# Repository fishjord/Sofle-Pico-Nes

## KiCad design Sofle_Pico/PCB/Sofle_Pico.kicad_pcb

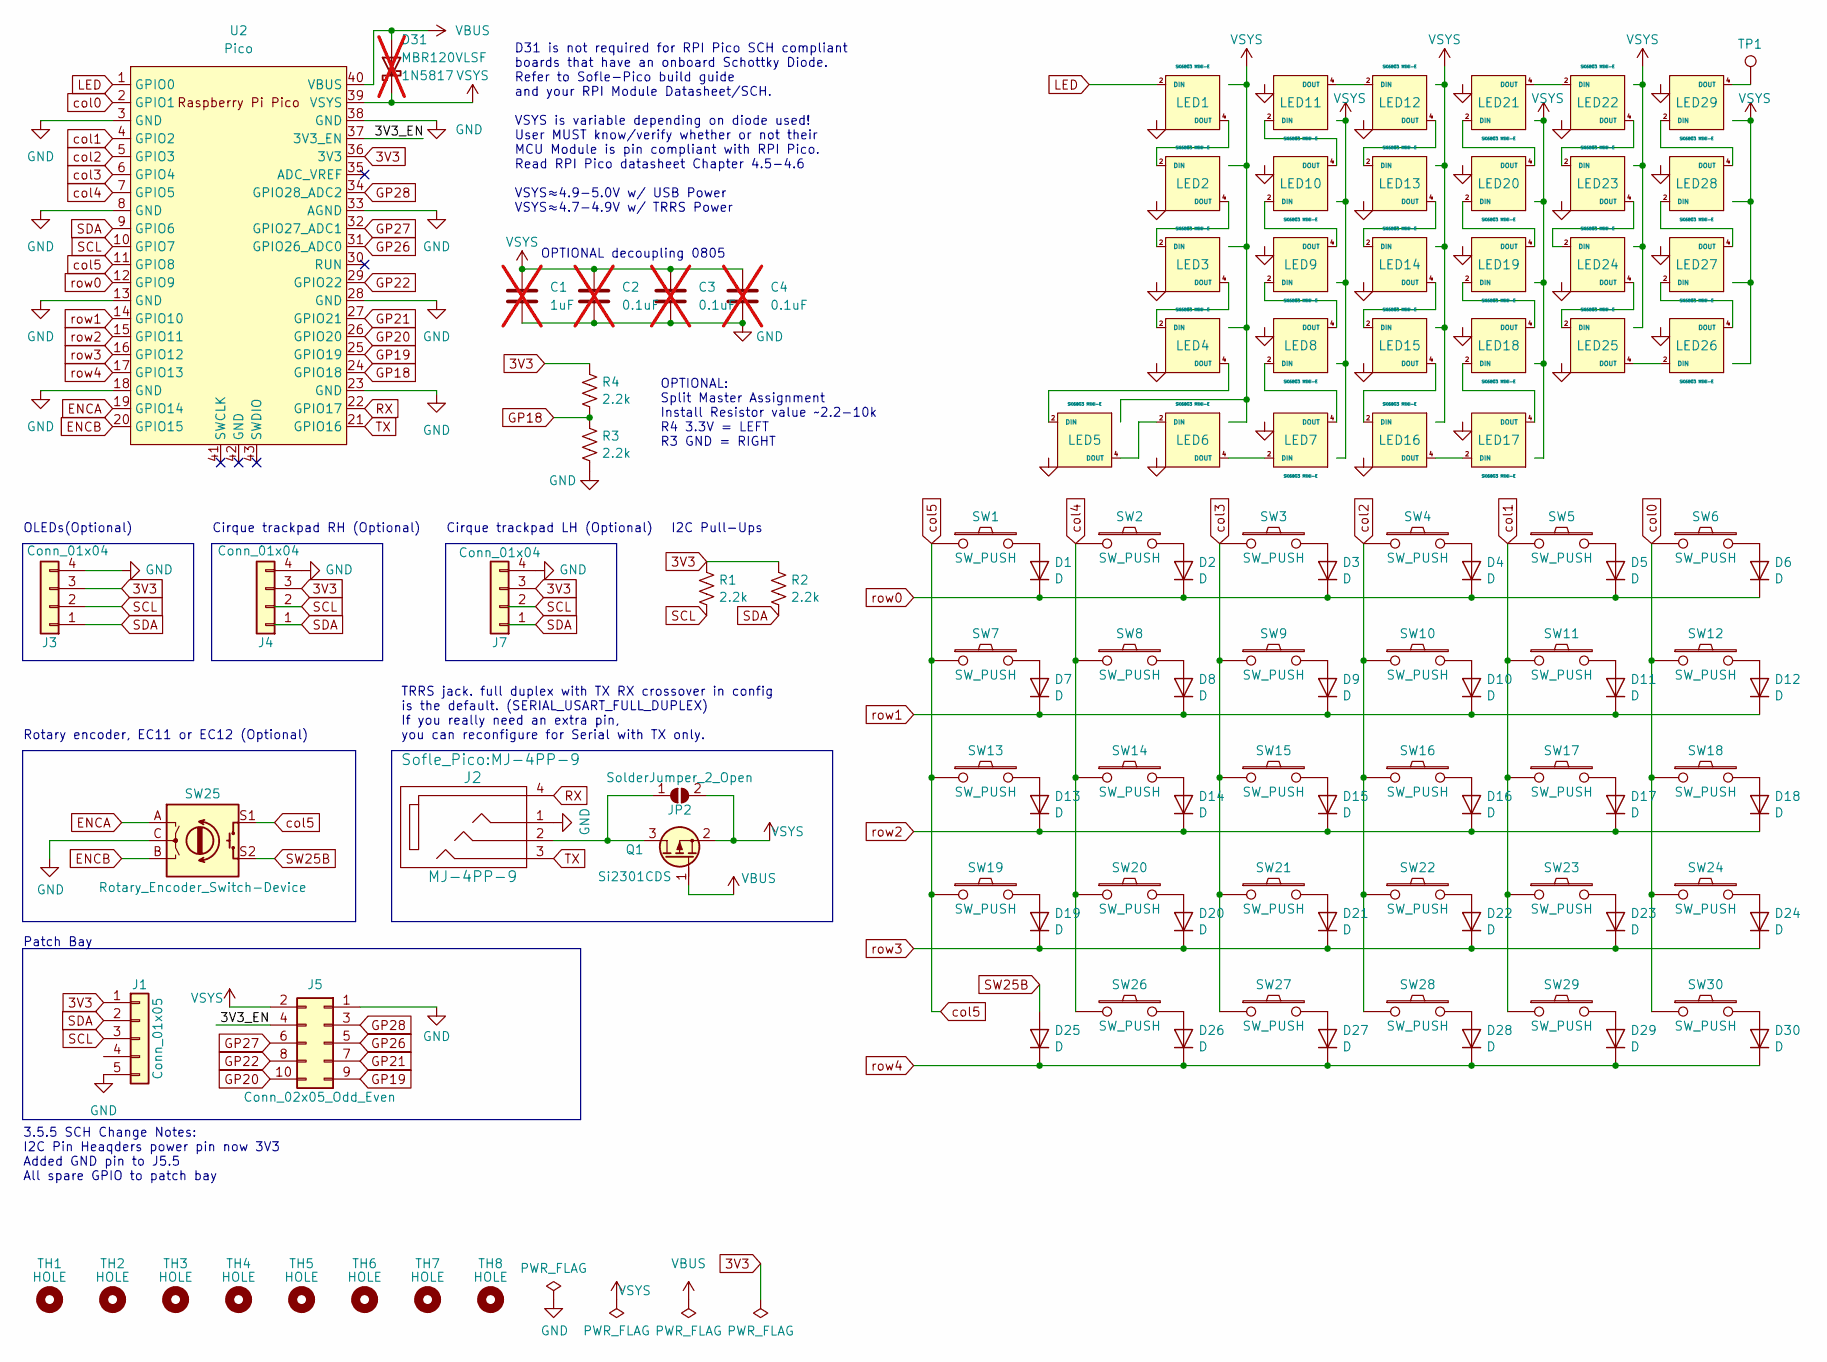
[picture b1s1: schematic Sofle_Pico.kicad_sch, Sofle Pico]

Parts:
C1: 1uF; C_0805_2012Metric_Pad1.18x1.45mm_HandSolder; Tolerance (%) 10; Voltage Rating 50V; MFG PN CL21B105KBFNNNE; JLCPCB_PN C28323; not fitted
C2, C3, C4: 0.1uF; C_0805_2012Metric_Pad1.18x1.45mm_HandSolder; Tolerance (%) 10; Voltage Rating 50V; MFG PN CC0805KRX7R9BB104; JLCPCB_PN C49678; not fitted
D1, D2, D3, D4, D5, D6, D7, D8, D9, D10, D11, D12, D13, D14, D15, D16, D17, D18, D19, D20, D21, D22, D23, D24, D25, D26, D27, D28, D29, D30: D; D_SOD-123_DO-35_Hybrid_DoubleSided_V2; Voltage Rating 75v; MFG PN 1N4148W; JLCPCB_PN C81598
D31: MBR120VLSF; D_SOD-123_DO-41_7.62mm_Hybrid_DoubleSided; not fitted
J1: Conn_01x05; Pimaroni_PinHeader_1x05_P2.54mm_Vertical Sofle v3b
J2: MJ-4PP-9
J3: Conn_01x04; OLED SSD1306 128x64
J4, J7: Conn_01x04; Cirque tie in
J5: Conn_02x05_Odd_Even; PinHeader_2x05_P2.54mm_Vertical
JP2: SolderJumper_2_Open; Level Shifter Bypass Jumper
LED1, LED2, LED3, LED4, LED5, LED6, LED7, LED8, LED9, LED10, LED11, LED12, LED13, LED14, LED15, LED16, LED17, LED18, LED19, LED20, LED21, LED22, LED23, LED24, LED25, LED26, LED27, LED28, LED29: SK6803 MINI-E; SK6803_MINI-E_v3.5.5
Q1: Si2301CDS; SOT-23; JLCPCB_PN C10487
R1, R2, R3, R4: 2.2k; Res_1206_SMD_6.3mm_TH_Hybrid
SW1, SW2, SW3, SW4, SW5, SW6, SW7, SW8, SW9, SW10, SW11, SW12, SW13, SW14, SW15, SW16, SW17, SW18, SW19, SW20, SW21, SW22, SW23, SW24, SW26, SW27, SW28, SW29, SW30: SW_PUSH; Cherry_MX_DS_Hotswap_v3.5.4
SW25: Rotary_Encoder_Switch-Device; RotaryEncoder_Alps_EC11E-Switch_Vertical_H20mm-keebio_modif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
TH1, TH2, TH7: HOLE; Hole from sofle for M2 posts gold rimmer wide-keyplate-hole
TH3, TH4, TH5, TH6, TH8: HOLE; Hole from sofle for M2 posts gold rimmer
TP1: TestPoint; TestPoint_THTPad_2.0x2.0mm_Drill1.0mm; JLCPCB_PN C94111
U2: Pico; RPi_Pico_SMD_TH_DS

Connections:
3V3: J1.1, J3.3, J4.3, J7.3, R1.1, R2.1, R4.2, U2.36 (3V3)
/3V3_EN: J5.4, U2.37 (3V3_EN)
ENCA: SW25.A, U2.19 (GPIO14)
ENCB: SW25.B, U2.20 (GPIO15)
GND: C1.2, C2.2, C3.2, C4.2, J1.5, J2.1, J3.4, J4.4, J5.1, J7.4, LED1.1 (GND), LED2.1 (GND), LED3.1 (GND), LED4.1 (GND), LED5.1 (GND), LED6.1 (GND), LED7.1 (GND), LED8.1 (GND), LED9.1 (GND), LED10.1 (GND), LED11.1 (GND), LED12.1 (GND), LED13.1 (GND), LED14.1 (GND), LED15.1 (GND), LED16.1 (GND), LED17.1 (GND), LED18.1 (GND), LED19.1 (GND), LED20.1 (GND), LED21.1 (GND), LED22.1 (GND), LED23.1 (GND), LED24.1 (GND), LED25.1 (GND), LED26.1 (GND), LED27.1 (GND), LED28.1 (GND), LED29.1 (GND), R3.2, SW25.C, U2.3 (GND), U2.8 (GND), U2.13 (GND), U2.18 (GND), U2.23 (GND), U2.28 (GND), U2.33 (AGND), U2.38 (GND)
GP18: R3.1, R4.1, U2.24 (GPIO18)
GP19: J5.9, U2.25 (GPIO19)
GP20: J5.10, U2.26 (GPIO20)
GP21: J5.7, U2.27 (GPIO21)
GP22: J5.8, U2.29 (GPIO22)
GP26: J5.5, U2.31 (GPIO26_ADC0)
GP27: J5.6, U2.32 (GPIO27_ADC1)
GP28: J5.3, U2.34 (GPIO28_ADC2)
LED: LED1.2 (DIN), U2.1 (GPIO0)
unnamed: D1.2 (A), SW1.2
unnamed: D2.2 (A), SW2.2
unnamed: D3.2 (A), SW3.2
unnamed: D4.2 (A), SW4.2
unnamed: D5.2 (A), SW5.2
unnamed: D6.2 (A), SW6.2
unnamed: D7.2 (A), SW7.2
unnamed: D8.2 (A), SW8.2
unnamed: D9.2 (A), SW9.2
unnamed: D10.2 (A), SW10.2
unnamed: D11.2 (A), SW11.2
unnamed: D12.2 (A), SW12.2
unnamed: D13.2 (A), SW13.2
unnamed: D14.2 (A), SW14.2
unnamed: D15.2 (A), SW15.2
unnamed: D16.2 (A), SW16.2
unnamed: D17.2 (A), SW17.2
unnamed: D18.2 (A), SW18.2
unnamed: D19.2 (A), SW19.2
unnamed: D20.2 (A), SW20.2
unnamed: D21.2 (A), SW21.2
unnamed: D22.2 (A), SW22.2
unnamed: D23.2 (A), SW23.2
unnamed: D24.2 (A), SW24.2
unnamed: D26.2 (A), SW26.1
unnamed: D27.2 (A), SW27.2
unnamed: D28.2 (A), SW28.2
unnamed: D29.2 (A), SW29.2
unnamed: D30.2 (A), SW30.2
unnamed: J2.2, JP2.1 (A), Q1.3 (D)
unnamed: LED1.4 (DOUT), LED2.2 (DIN)
unnamed: LED2.4 (DOUT), LED3.2 (DIN)
unnamed: LED3.4 (DOUT), LED4.2 (DIN)
unnamed: LED4.4 (DOUT), LED5.2 (DIN)
unnamed: LED5.4 (DOUT), LED6.2 (DIN)
unnamed: LED6.4 (DOUT), LED7.2 (DIN)
unnamed: LED7.4 (DOUT), LED8.2 (DIN)
unnamed: LED8.4 (DOUT), LED9.2 (DIN)
unnamed: LED9.4 (DOUT), LED10.2 (DIN)
unnamed: LED10.4 (DOUT), LED11.2 (DIN)
unnamed: LED11.4 (DOUT), LED12.2 (DIN)
unnamed: LED12.4 (DOUT), LED13.2 (DIN)
unnamed: LED13.4 (DOUT), LED14.2 (DIN)
unnamed: LED14.4 (DOUT), LED15.2 (DIN)
unnamed: LED15.4 (DOUT), LED16.2 (DIN)
unnamed: LED16.4 (DOUT), LED17.2 (DIN)
unnamed: LED17.4 (DOUT), LED18.2 (DIN)
unnamed: LED18.4 (DOUT), LED19.2 (DIN)
unnamed: LED19.4 (DOUT), LED20.2 (DIN)
unnamed: LED20.4 (DOUT), LED21.2 (DIN)
unnamed: LED21.4 (DOUT), LED22.2 (DIN)
unnamed: LED22.4 (DOUT), LED23.2 (DIN)
unnamed: LED23.4 (DOUT), LED24.2 (DIN)
unnamed: LED24.4 (DOUT), LED25.2 (DIN)
unnamed: LED25.4 (DOUT), LED26.2 (DIN)
unnamed: LED26.4 (DOUT), LED27.2 (DIN)
unnamed: LED27.4 (DOUT), LED28.2 (DIN)
unnamed: LED28.4 (DOUT), LED29.2 (DIN)
unnamed: LED29.4 (DOUT), TP1.1
RX: J2.4, U2.22 (GPIO17)
SCL: J1.3, J3.2, J4.2, J7.2, R1.2, U2.10 (GPIO7)
SDA: J1.2, J3.1, J4.1, J7.1, R2.2, U2.9 (GPIO6)
SW25B: D25.2 (A), SW25.S2
TX: J2.3, U2.21 (GPIO16)
VBUS: D31.2 (A), Q1.1 (G), U2.40 (VBUS)
VSYS: C1.1, C2.1, C3.1, C4.1, D31.1 (K), J5.2, JP2.2 (B), LED1.3 (VDD), LED2.3 (VDD), LED3.3 (VDD), LED4.3 (VDD), LED5.3 (VDD), LED6.3 (VDD), LED7.3 (VDD), LED8.3 (VDD), LED9.3 (VDD), LED10.3 (VDD), LED11.3 (VDD), LED12.3 (VDD), LED13.3 (VDD), LED14.3 (VDD), LED15.3 (VDD), LED16.3 (VDD), LED17.3 (VDD), LED18.3 (VDD), LED19.3 (VDD), LED20.3 (VDD), LED21.3 (VDD), LED22.3 (VDD), LED23.3 (VDD), LED24.3 (VDD), LED25.3 (VDD), LED26.3 (VDD), LED27.3 (VDD), LED28.3 (VDD), LED29.3 (VDD), Q1.2 (S), U2.39 (VSYS)
col0: SW6.1, SW12.1, SW18.1, SW24.1, SW30.1, U2.2 (GPIO1)
col1: SW5.1, SW11.1, SW17.1, SW23.1, SW29.1, U2.4 (GPIO2)
col2: SW4.1, SW10.1, SW16.1, SW22.1, SW28.1, U2.5 (GPIO3)
col3: SW3.1, SW9.1, SW15.1, SW21.1, SW27.1, U2.6 (GPIO4)
col4: SW2.1, SW8.1, SW14.1, SW20.1, SW26.2, U2.7 (GPIO5)
col5: SW1.1, SW7.1, SW13.1, SW19.1, SW25.S1, U2.11 (GPIO8)
row0: D1.1 (K), D2.1 (K), D3.1 (K), D4.1 (K), D5.1 (K), D6.1 (K), U2.12 (GPIO9)
row1: D7.1 (K), D8.1 (K), D9.1 (K), D10.1 (K), D11.1 (K), D12.1 (K), U2.14 (GPIO10)
row2: D13.1 (K), D14.1 (K), D15.1 (K), D16.1 (K), D17.1 (K), D18.1 (K), U2.15 (GPIO11)
row3: D19.1 (K), D20.1 (K), D21.1 (K), D22.1 (K), D23.1 (K), D24.1 (K), U2.16 (GPIO12)
row4: D25.1 (K), D26.1 (K), D27.1 (K), D28.1 (K), D29.1 (K), D30.1 (K), U2.17 (GPIO13)

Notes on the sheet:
Cirque trackpad RH (Optional)
I2C Pull-Ups
TRRS jack. full duplex with TX RX crossover in config is the default. (SERIAL_USART_FULL_DUPLEX) If you really need an extra pin, you can reconfigure for Serial with TX only.
Rotary encoder, EC11 or EC12 (Optional)
D31 is not required for RPI Pico SCH compliant boards that have an onboard Schottky Diode. Refer to Sofle-Pico build guide and your RPI Module Datasheet/SCH. VSYS is variable depending on diode used! User MUST know/verify whether or not their MCU Module is pin compliant with RPI Pico. Read RPI Pico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
OPTIONAL: Split Master Assignment Install Resistor value ~2.2-10k R4 3.3V = LEFT R3 GND = RIGHT
OLEDs(Optional)
Patch Bay
Cirque trackpad LH (Optional)
OPTIONAL decoupling 0805
3.5.5 SCH Change Notes: I2C Pin Heaqders power pin now 3V3 Added GND pin to J5.5 All spare GPIO to patch bay

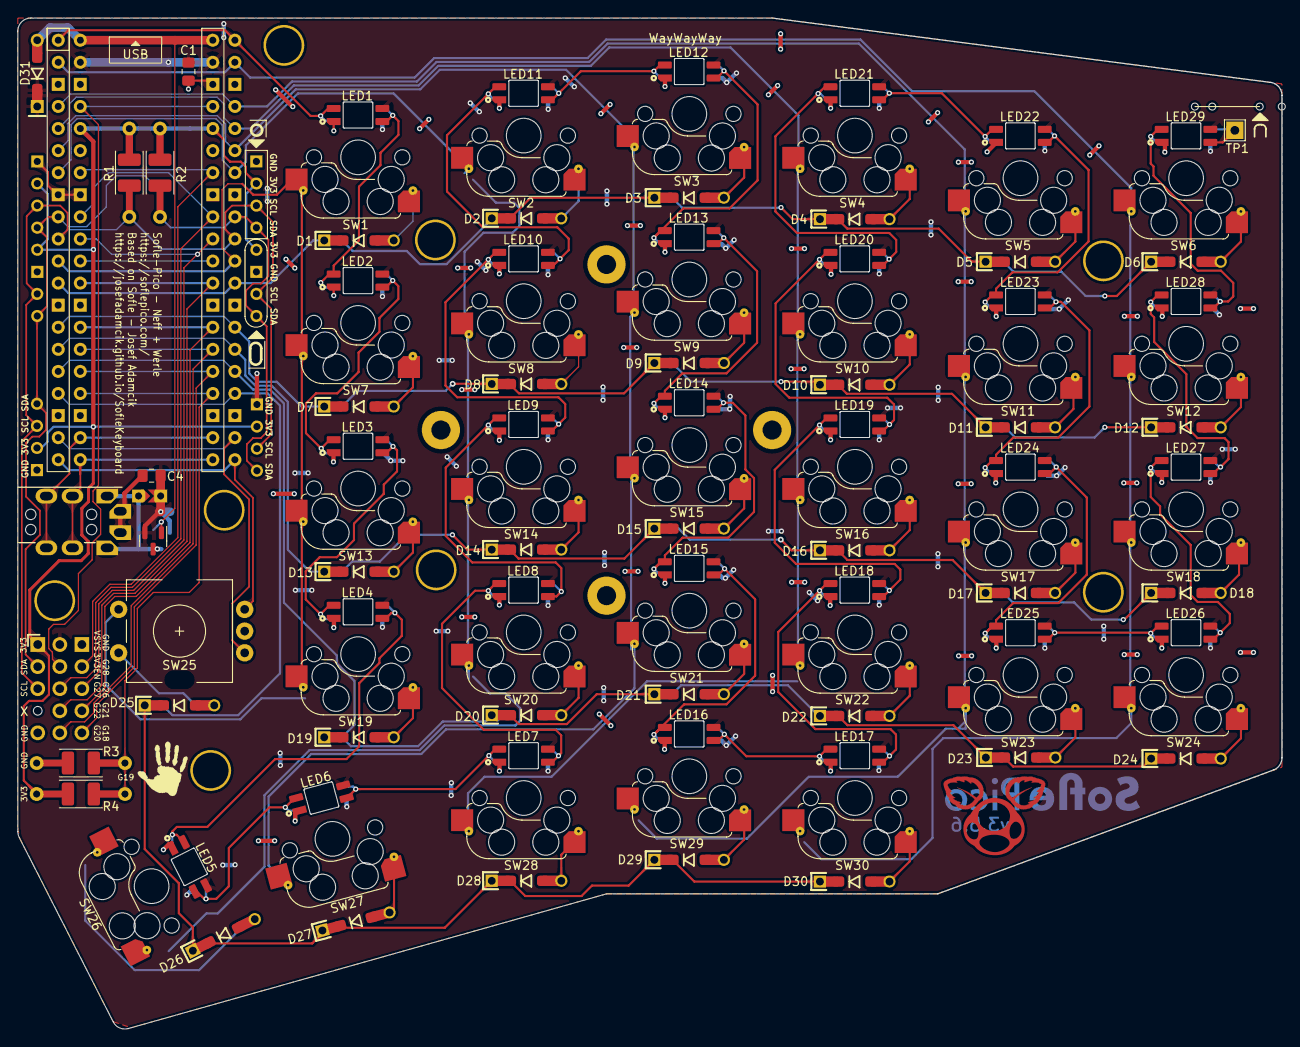
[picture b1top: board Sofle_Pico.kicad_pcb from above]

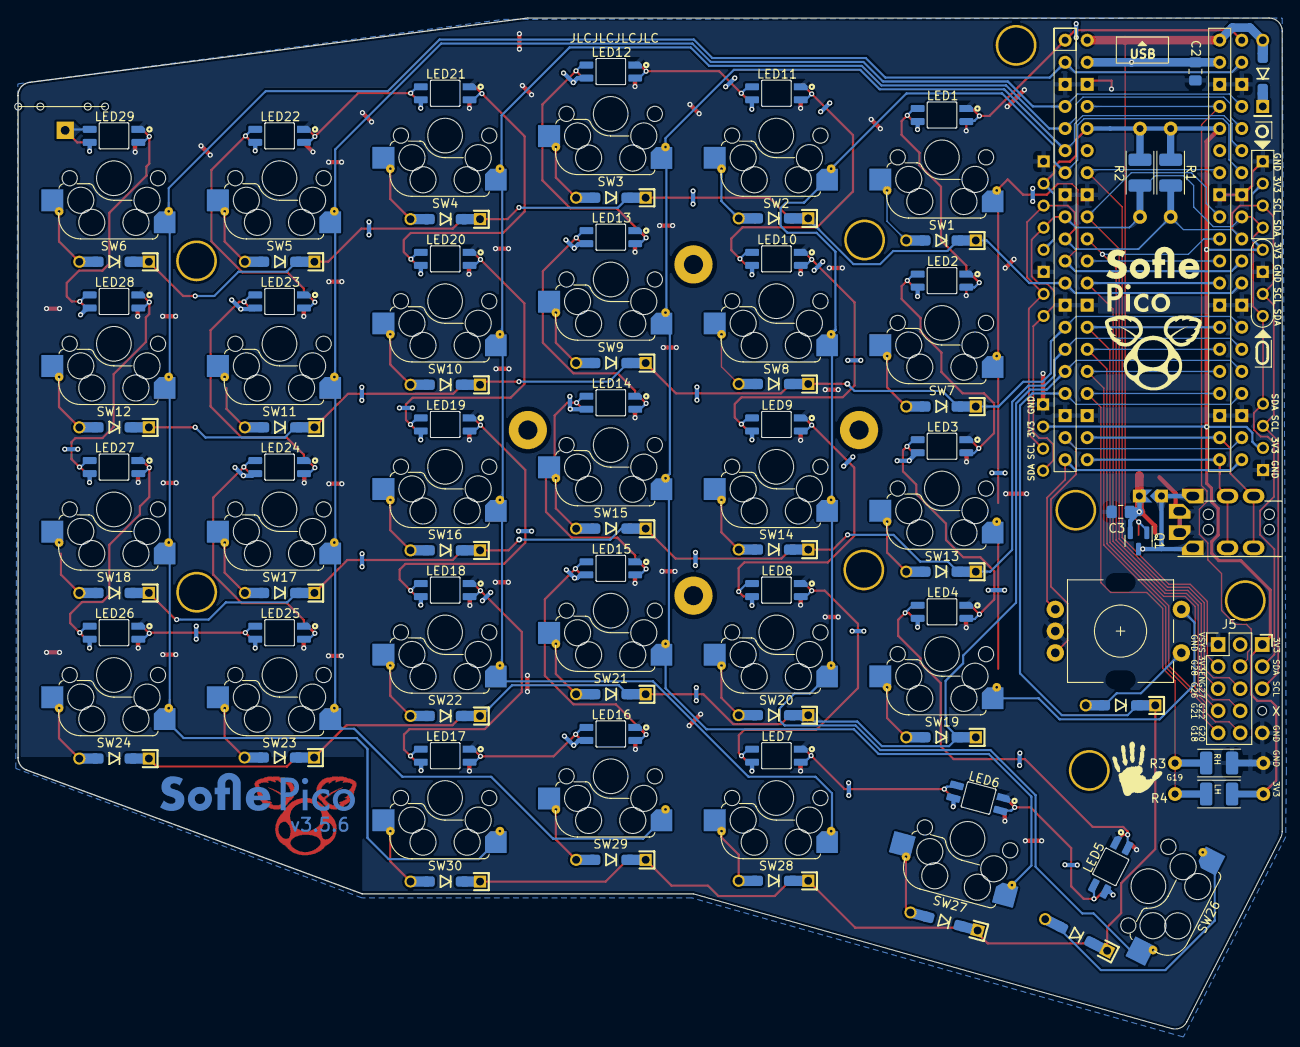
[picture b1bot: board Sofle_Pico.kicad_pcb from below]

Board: 2 copper layers, 145.4 x 116.3 mm, 117 parts (96 on the bottom side), 91 nets.

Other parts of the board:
STP**: Cirque_40mm_OLED_RH

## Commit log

2025-10-24 Split 3d printable cases into sub-directories for stls and draft quality slice files.
2025-10-24 Create a back plate model that doesn't have a tenting puck hole.
2025-10-24 Create higher quality slice files for the keyplate.
2025-10-24 Create a plate foam svg for the backplate.
2025-10-24 Upgrade to kicad 9.0 project and fix name in schematic to remove choc.
2025-10-24 Remove tenting puck from the pcb.
2025-10-24 Remove choc version of the pico.
2025-10-24 Add keyplate 3d printing model without holes for a tenting kit.
2025-10-24 WIP 3d printed cirque mount
2025-10-25 Create a 3d model for the cirque trackpad mount.
2025-10-25 Add helper discs to the puckless backplate printer-ready gcode files.
2025-10-25 Add helper disks to the quality keyplate printer ready gcode files.
2025-10-25 Add a draft quality 3d printer ready mount for the 40mm cirque trackpad.
2025-10-25 Reslice RH plate
2025-10-26 Rename printer-ready models to group tenting and no-tenting together.
2025-10-27 Update the no tenting puck quality models to use the notched keyplates and add a brim.
2025-10-27 Update cirque trackpad mount to project the ring down to the plate.
2025-10-30 Regenerate gcode for print ready using 0.20mm layer height
2025-10-30 Update board schematic silk screen to fully encapsulate diodes and switch on one side with lines
2025-10-30 Add production ready gcode files for 3d printed keyplate without tenting mount holes.
2025-10-30 Reslice for Prusa MK3S
2025-10-31 Hack up the pcb file and generate backplate foam that has cutouts for the hotswap sockets, LEDs, and diodes
2025-11-01 Move STL files to a dedicated directoy under the 3d printable case directory.
2025-11-01 Add a brimmed gcode file for the oled case plates.
2025-11-01 Update back plate foam to include cutouts for the kailh socket legs.
2025-11-01 Nudge diode cutouts for the below-switch diodes up a bit.
2025-11-01 Add a LH version of the component cutout platefoam.
2025-11-01 Remove duplicate lines from platefoam outlines
2025-11-02 Add a cirque mount and foam cutouts to support it over the pi pico
2025-11-02 Add cutouts for aceirmc RP2040 to the support.
2025-11-02 Create a oled plate with M2 mounting holes.
2025-11-05 Add right and left handed versions of the oled with mounting holes
2025-11-09 Rotate cirque mount nub to be on the other side of the mounting ring so that the trackpad is 'right side up'
2025-11-11 Move cirque production ready models to a dedicated directory resliced with variable layer height
2025-11-12 Add a cirque mount 3d printed case models.
2025-11-12 Add backplate foam with hotswap switch cutouts
2025-11-12 Create a oled plate model with M2 mounting holes.
2025-11-16 Create a backplate model with a post
2025-12-09 Add a missing route to the TSSR transistor on F.Cu.
2025-12-12 Add a missing trace on F.Cu for the TSSR transistor VSYS terminal
